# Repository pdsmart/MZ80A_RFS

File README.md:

## Overview

The Sharp MZ80A came with 48K RAM and 4K ROM and apart from the option to add a 2K User RAM/ROM and a 4K Floppy Drive ROM, there was no further possibility to expand the machine memory
capabilities at the hardware level and thus no additional firmware could be added for use at power-on. Add-ons had to rely on loading control firmware into RAM via tape or floppy, thus depleting valuable application space. Some machines of the same era
utilised a scheme called 'banking' whereby much larger memories would occupy a smaller block within the CPU address space and be selected according to features required and hardware attached. The 
BBC Micro was such a machine with upto 16 banks of 16Kb, it made the machine much more useable.

One of the seperate projects I've been working on was a 40/80 Column switchable display and colour output. This upgrade requires different software, either a complete rewrite of the original
monitor or a patched copy for 80 column mode. Wanting to keep the machine as original as possible, using a rewritten ROM is out of the question thus I would need 2 ROMS, original for 40Column
and a patched one for 80Column.

Thus was born the need for Rom Paging in the Sharp MZ80A, ie. Use a modern Flash RAM to house multiple 4K Roms which can be *switched in* to the 4K Monitor ROM address space according to the
hardware upgrade being used.

It was also seen when using large Flash RAM's it was possible to store programs that would normally be present on tape or floppy and load at much higher speed making use of the computer that
much easier.

This upgrade goes a bit further and uses the 4K Monitor ROM and 2K User ROM space to map in 2x512Kbyte Flash RAM's providing multiple paged roms (theoretical 256 x 2K slots and 128 x 4K slots)
and the required custom software to control the banking called the Rom Filing System.

This page along with the [CP/M](/sharpmz-upgrades-cpm) page forms the start of the RFS documentation which is still in its infancy. Within this repository are the schematics, PCB Gerber files and the software to implement the Rom Filing
System hardware and software.

## Rom Filing System

The Rom Filing System is a hardware and software upgrade for the Sharp MZ80A. The hardware replaces the Monitor and User ROM's on the motherboard by a daughter card with lifter sockets where 2x512Kbyte Flash RAM's are sited.
One of the Flash RAM's is paged into the Monitor ROM socket and the other into the User ROM socket. The first 32Kbytes (8 slots x 4K) of the Monitor Flash RAM and the first 24Kybtes (12 slots of 2K) of the User Flash RAM is
dedicated to paged ROMs with the remainder being used to store Sharp MZF format binary images compacted within 256byte sectors. (*NB. This may change to 128 byte sectors as the original reason for choosing 256 byte
sectors no longer exists*).

### RFS Hardware

It is quite easy to make upgrades for older tech these days by using one of the plethora of ready made development boards such as the Raspberry Pi or standalone microcontrollers such as the STM32 series. I did consider using an STM32F series
microcontroller as a ROM emulator as they have the price, performance and packaging advantages but then the goal of this project and the goals of the other Sharp MZ80A upgrades (excluding the Tranzputer) was to use old tech and keep the machine
original. Unlike a commercial project where part choice to provide the required functionality is imperative to keep costs low, with this project the focus is on the learning journey using parts such as the 74 series which were available at the
time of the Sharp, excepting of course the larger Flash RAM and Static RAMs which came a few years later but necessary for the functionality.

Version 2 of the hardware builds on the experiences learnt making version 1. It adds a coded latch (a programmable number of reads required in the 0xEFF8-0xEFFF region) in order to enable access to the control registers and I/O otherwise
both read and write access is performed on memory. It also adds two additional (optional) memories for increased storage and RAM. The additional two devices can be both Flash RAM or 1 Flash RAM and 1 Static RAM. The Static RAM is to
increase the capability of CP/M, such as number of SD drives available and the memory available to TPA applications.

The schematic has been split into two distinct functions, Memory and Control logic. Above is the new Memory schematic which retains the single 512K Flash RAM which replaces the Monitor ROM, write access is not possible as the underlying
Sharp hardware blocks write on Monitor ROM select. In the User ROM socket are 3 devices, the 512K Flash RAM from version 1 but with write access and an additional 2 devices.

The second schematic is the control logic. This creates the needed memory select lines from the main board in combination with address decoding and programmable latches for the upper address lines.

A coded latch is added (74HCT191) which only enables I/O when a read is made to the region 0xEFF8-0xEFFF for a programmable number of times, set by the latch U14 bits 3:5. At start up these bits will be 0 and to enable the I/O a read 
will be needed in the region 0xE800-exEFF7 to reset the 74HCT191 which must then be followed by 16 reads to the range 0xEFF8-0xEFFF. Once the I/O is enabled, the latch value can be changed along with other registers. As soon as a read is made
into the region 0xE800-0xEFF7 then the I/O control is disabled and reads/writes are sent to the selected memory device.

In addition it adds 2 SPI circuits, only one of which will be assembled on the PCB according to choice. The first is a software bitbang SPI using the Z80 to form the correct serial and clock signals in order to talk to an SD Card.
This method uses few hardware components but is much slower. The second is a hardware SPI running at 8MHz which is capable of transferring/receiving a byte in less time that the Z80 takes to perform a read, this allows for performance
similar to the Flash RAM storage. On the hardware SPI it is possible via U14 bit 0 to manually clock the SPI logic, this is intentional as initial connections with an SD Card should begin at 100KHz or less, once established and parameters
set then the 8MHz hardware clock is used.

### RFS Software

In order to use the RFS Hardware, a comprehensive set of Z80 assembler methods needed to be written to allow bank paging and with it came the option, which was taken, to upgrade the machines monitor functionality. This Z80
software forms the Rom Filing System which can be found in the repository within the \<software\> directory.

The following table describes each major file which forms the Rom Filing System:

| Module                 | Target ROM | Size | Bank | Description                                                                                                                                                             |
|------------------------|------------|------|------|-------------------------------------------------------------------------------------------------------------------------------------------------------------------------|
| rfs.asm                | User       | 2K   | 0    | Primary Rom Filing System and MZ700/MZ800 Monitor tools.                                                                                                                |
| rfs_bank1.asm          | User       | 2K   | 1    | Floppy disk controller functions.                                                                                                                                       |
| rfs_bank2.asm          | User       | 2K   | 2    | SD Card controller functions.                                                                                                                                           |
| rfs_bank3.asm          | User       | 2K   | 3    | Memory monitor utility functions and tape/SD copy utilities.                                                                                                            |
| rfs_bank4.asm          | User       | 2K   | 4    | CMT functions.                                                                                                                                                          |
| rfs_bank5.asm          | User       | 2K   | 5    | Unused.                                                                                                                                                                 |
| rfs_bank6.asm          | User       | 2K   | 6    | Message printing routines, static messages, ascii conversion and help screen.                                                                                           |
| rfs_bank7.asm          | User       | 2K   | 7    | Memory Test utility and 8253 Timer test.                                                                                                                                |
| cbios_bank1.asm        | User       | 2K   | 8    | CPM CBIOS Utilities and Audio functions.                                                                                                                                |
| cbios_bank2.asm        | User       | 2K   | 9    | CPM CBIOS Screen and ANSI Terminal functions.                                                                                                                           |
| cbios_bank3.asm        | User       | 2K   | 10   | CPM CBIOS SD Card Controller functions.                                                                                                                                 |
| cbios_bank4.asm        | User       | 2K   | 11   | CPM CBIOS Floppy Disk Controller functions.                                                                                                                             |
| monitor_SA1510.asm     | Monitor    | 4K   | 0    | Original SA1510 Monitor for 40 character display.                                                                                                                       |
| monitor_80c_SA1510.asm | Monitor    | 4K   | 1    | Original SA1510 Monitor patched for 80 character display.                                                                                                               |
| cbios.asm              | Monitor    | 4K   | 2    | CPM CBIOS (exec location 0xC000:0xCFFFF).                                                                                                                               |
| rfs_mrom.asm           | Monitor    | 4K   | 3    | Rom Filing System helper functions located in the Monitor ROM space in Bank 3. These functions are used to scan and process MZF files stored within the User ROM space. |
| unassigned             | Monitor    | 4K   | 4    | Unused slot.                                                                                                                                                            |
| unassigned             | Monitor    | 4K   | 5    | Unused slot.                                                                                                                                                            |
| unassigned             | Monitor    | 4K   | 6    | Unused slot.                                                                                                                                                            |
| unassigned             | Monitor    | 4K   | 7    | Unused slot.                                                                                                                                                            |

In the User ROM, the rfs.asm module and  all the rfs_bank\<x\>.asm modules form the Rom Filing System and are invoked by the original SA-1510 monitor on startup of the MZ80A (or reset). The functionality in these files provides
the Rom Filing System and additional MZ700/800 style monitor utilities. The way the code is structured, a call can be made from one bank to another without issue (stack and execution point manipulation is taken care of) thus
providing almost 16K program space in the User ROM slot.

Sharing the User ROM banks are the cbios_bank\<x\>.asm modules which form part of the CP/M Custom BIOS. They extend the functionality of the CBIOS without impacting RAM usage which is crucial within CP/M in order
to run as many applications as possible.
  
In the Monitor ROM, the rfs_mrom.asm module is located within the 4th bank (bank 3, bank 0 = original SA1510 ROM, bank 1 = 80 column modified SA1510 ROM) and provides utilities needed by the Rom Filing
System. These utilities are specifically needed for scanning and loading MZF files stored in the User ROM Flash RAM (because code executing in the User ROM cant page itself out to scan the
remainder of the ROM).

CPM v2.2 has been added with the CBIOS (Custom BIOS) being implemented within an MROM Bank (bank 2) along with User ROM Banks 8-11 mentioned above. This saves valuable RAM leaving only the CPM CCP and BDOS in RAM which can
be overwritten by programs, this gives a feasible 47K of useable program RAM. An intention is to include a paged RAM chip in the next release of the RFS Hardware which will allow upto 52K of program RAM.

There are several rapidly written shell scripts to aid in the building of the RFS software (which in all honesty need to be written into a single Python or Java tool). These can be seen in the following table along with their purpose:

| Script            |  Description                                                                                                             |
|------------------ | ------------------------------------------------------------------------------------------------------------------------ |
| assemble_cpm.sh   | A shell script to build the CPM binary, the CPM MZF format application for loading via RFS and the CPM ROM Drives 0 & 1  |
| assemble_rfs.sh   | A bash script to build the Rom Filing System ROM images.                                                                 |
| assemble_roms.sh  | A bash script to build all the standard MZ80A ROMS, such as the SA-1510 monitor ROM.                                     |
| make_roms.sh      | A bash script to build the RFS ROMS suitable for programming in the 512KByte Flash RAMS. These images contain the banked RFS ROMS, the various system ROMS such as SA-1510 and all the MZF programs to be loaded by the RFS. |
| make_cpmdisks.sh  | A bash script to build a set of CPM disks, for use as Raw images in the SD Card or Rom drives and as CPC Extended Disk Formats for use in a Floppy disk emulator or copying to physical medium. |
| make_sdcard.sh    | A bash script to create an SD card image combining the RFS Image and several CPM disk drives. This image is then binary copied onto the SD card and installed into the RFS SD Card reader. |
| mzftool.pl        | A perl script to create/extract and manipulate MZF images.                                                               |
| processMZFfiles.sh| A bash script to convert a set of MZF programs into sectored images suitable for use in the Rom Filing System ROMS.      |
| sdtool            | A binary created from the src/tools repository which builds the RFS SD Card image, creating a directory and adding MZF/Binary applications into the drive image. |

To build the software, the assemble_\<name\> shell scripts are used. These scripts requires the [GLASS Z80 Assembler](https://bitbucket.org/grauw/glass/src/default/) which is freely downloadable.

The procedure to build a ROM is:-<br/>
1. Take a set of MZF files and convert them into correct sector padded binary files. The proc_mzf.sh file takes a directory and processes all files within it, transforming originalfile.mzf to originalfile.mzf.\<sector size>.bin<br/>
2. Build the Z80 code using \<tools\>/assemble_rfs.sh for the RFS components, \<tools\>/assemble_roms.sh for assembling all original ROM source including the SA1510 monitor ROM, \<tools\>/assemble_cpm.sh for
   assembling the CPM binaries and dependencies.<br/>
3. Build the ROM using the \<tools\>/make_roms.sh script - before using this you need to create your own selection of MZF files by listing the files with ls -l then converting them into a set of ROM_INCLUDE variables for programs that
   will go into the User and Monitor Flash RAM's.<br/>

### RFS Monitor
  
Upon boot, the typical SA-1510 monitor signon banner will appear and be appended with "+ RFS" if all works well. The usual '\* ' prompt appears and you can then issue any of the original SA-1510 commands along with a set of enhanced
commands, some of which were seen on the MZ700/ MZ800 range and others are custom. The full set of commands are listed in the table below:

| Command | Parameters                          | Description                                                                        |
|---------|-------------------------------------|------------------------------------------------------------------------------------|
| 4       | n/a                                 | Switch to 40 Character mode if the 40/80 Column display upgrade has been added\.   |
| 8       | n/a                                 | Switch to 80 Character mode if the 40/80 Column display upgrade has been added\.   |
| B       | n/a                                 | Enable/Disable key entry beep\.                                                    |
| C       | \[\<8 bit value\>\]                 | Initialise memory from 0x1200 \- Top of RAM with 0x00 or provided value\.          |
| D       | \<address>\[\<address2>\]           | Dump memory from \<address> to \<address2> (or 20 lines) in hex and ascii. When a screen is full, the output is paused until a key is pressed\. <br><br>Subsequent 'D' commands without an address value continue on from last displayed address\.<br><br> Recognised keys during paging are:<br> 'D' - page down, 'U' - page up, 'X' - exit, all other keys list another screen of data\.|
| EC      | \<name> or <br>\<file number>       | Erase file from SD Card\. The SD Card is searched for a file with \<name> or \<file number> and if found, erased\. |
| F       | \[\<drive number\>\]                | Boot from the given Floppy Disk, if no disk number is given, you will be prompted to enter one\. |
| f       | n/a                                 | Execute the original Floppy Disk AFI code @ 0xF000                                 |
| H       | n/a                                 | Help screen of all these commands\.                                                |
| IR      | n/a                                 | Paged directory listing of the files stored in ROM\. Each file title is preceded with a hex number which can be used to identify the file\. |
| IC      | n/a/                                | Paged directory listing of the files stored on the SD Card\. Each file title is preceded with a hex number which can be used to identify the file\. |
| J       | \<address>                          | Jump \(start execution\) at location \<address>\.                                  |
| L \| LT | n/a                                 | Load file into memory from Tape and execute\.                                      |
| LTNX    | n/a                                 | Load file into memory from Tape, dont execute\.                                    |
| LR      | \<name> or <br>\<file number>       | Load file into memory from ROM\. The ROM is searched for a file with \<name> or \<file number> and if found, loaded and executed\. |
| LRNX    | \<name> or <br>\<file number>       | Load file into memory from ROM\. The ROM is searched for a file with \<name> or \<file number> and if found, loaded and not executed\. |
| LC      | \<name> or <br>\<file number>       | Load file into memory from SD Card\. The SD Card is searched for a file with \<name> or \<file number> and if found, loaded and executed\. |
| LCNX    | \<name> or <br>\<file number>       | Load file into memory from SD Card\. The SD Card is searched for a file with \<name> or \<file number> and if found, loaded and not executed\. |
| M       | \<address>                          | Edit and change memory locations starting at \<address>\.                          |
| P       | n/a                                 | Run a test on connected printer\.                                                  |
| R       | n/a                                 | Run a memory test on main mmemory\.                                                |
| S       | \<start addr> \<end addr> \<exec addr> | Save a block of memory to tape\. You will be prompted to enter the filename\. <br><br>Ie\. S120020001203 - Save starting at 0x1200 up until 0x2000 and set execution address to 0x1203\.  |
| SC      | \<start addr> \<end addr> \<exec addr> | Save a block of memory to SD Card\. You will be prompted to enter the filename\. |
| SD2T    | \<name> or <br>\<file number>       | Copy a file from SD Card to Tape\. The SD Card is searched for a file with \<name> or \<file number> and if found, copied to a tape in the CMT\. |
| T       | n/a                                 | Test the 8253 timer\.                                                              |
| T2SD    | n/a                                 | Copy a file from Tape onto the SD Card. A program is loaded from Tape and written to a free position in the SD Card\. |
| V       | n/a                                 | Verify a file just written to tape with the original data stored in memory         |

If the 40/80 column card is installed, typing '4' switches to 40 Column display, typing '8' switches to 80 Column display. For the directory listing commands, 4 columns of output will be shown when in 80 column mode.

## Building RFS

Building the Rom Filing System involves assembling the Z80 Assembly language source into a machine code binary and packaging it into an image suitable for writing onto a 512Kbyte Flash RAM. You may also want to include MZF applications
in the ROMS for rapid exection via the RFS system. If you intend to use CPM, see also the CPM documentation.

To accomplish it you need several tools and at the moment it is quite a manual process.

## Paths

For ease of reading, the following shortnames refer to the corresponding path in this chapter.

|  Short Name      |                                                                            |
|------------------|----------------------------------------------------------------------------|
| \[\<ABS PATH>\]  | The path where this repository was extracted on your system.               |
| \<software\>     | \[\<ABS PATH>\]/MZ80A_RFS/software                                         |
| \<roms\>         | \[\<ABS PATH>\]/MZ80A_RFS/software/roms                                    |
| \<CPM\>          | \[\<ABS PATH>\]/MZ80A_RFS/software/CPM                                     |
| \<tools\>        | \[\<ABS PATH>\]/MZ80A_RFS/software/tools                                   |
| \<src\>         | \[\<ABS PATH>\]/MZ80A_RFS/software/src                                      |
| \<MZF\>          | \[\<ABS PATH>\]/MZ80A_RFS/software/MZF                                     |
| \<MZB\>          | \[\<ABS PATH>\]/MZ80A_RFS/software/MZB                                     |

## Tools

All development has been made under Linux, specifically Debian/Ubuntu. I use Windows for flashing the RAM's and using the GUI version of CP/M Tools but havent dedicated any time into building the RFS under Windows. I will in due course
create a Docker image with all necessary tools installed, but in the meantime, in order to assemble the Z80 code, the C programs and work with the CP/M software andCP/M disk images, you will need to obtain and install the following tools.

[Z80 Glass Assembler](http://www.grauw.nl/blog/entry/740/) - A Z80 Assembler for converting Assembly files into machine code.<br>
[samdisk](https://simonowen.com/samdisk/)   - A multi-os command line based low level disk manipulation tool.<br>
[cpmtools](https://www.cpm8680.com/cpmtools/) - A multi-os command line CP/M disk manipulation tool.<br>
[CPMToolsGUI](http://star.gmobb.jp/koji/cgi/wiki.cgi?page=CpmtoolsGUI) - A Windows based GUI CP/M disk manipulation tool.<br>
[z88dk](https://www.z88dk.org/forum/) - An excellent C development kit for the Z80 CPU.<br>
[sdcc](http://sdcc.sourceforge.net/) - Another excellent Small Device C compiler, the Z80 being one of its targets. z88dk provides an enhanced (for the Z80) version of this tool within its package.<br>

## Software

Building the software and final ROM images can be done by cloning the [repository](https://github.com/pdsmart/MZ80A_RFS.git) and running some of the shell scripts and binaries provided.

The RFS is built as follows:

   1. Make the RFS binary using \<tools\>/assemble_rfs.sh, this creates \<roms\>/rfs.rom for the User Bank Flash RAM and \<roms\>/rfs_mrom.rom for the Monitor Bank Flash RAM.
   2. Make the original MZ80A monitor roms using \<tools\>/assemble_roms.sh, this creates \<roms\>/monitor_SA1510.rom and \<roms\>/monitor_80c_SA1510.rom for the Monitor Bank Flash RAM.
   3. Make the rom images using \<tools\>/make_roms.sh, this creates \<roms\>/USER_ROM_256.bin for the User Bank Flash RAM and \<roms\>/MROM_256.bin for the Monitor Bank Flash RAM.
      The rom images also contain a packed set of MZF applications found in the \<MZF\> directory. Edit the script \<tools\>/make_roms.sh to add or remove applications from the rom images.

The above procedure has been encoded in a set of shell scripts and C tools, which at the simplest level, is to run these commands:
````bash
cd <software>
tools/assemble_cpm.sh
tools/assemble_rfs.sh
tools/assemble_roms.sh
tools/make_cpmdisks.sh
tools/make_roms.sh
tools/make_sdcard.sh
````

The output of the above commands are ROM images \<roms\>/MROM_256.bin and \<roms\>/USER_ROM.256.bin which must be flashed into 512Kbyte Flash RAMS and inserted into the sockets on the
RFS adapter.

The applications which can be stored in the Flash RAMS are located in the \<MZF\> directory. In order to use them within the Flash RAM's, the applications need to be converted into sector rounded binary images and stored in the
\<MZB\> directory. The tool \<tool\>/processMZFiles.sh has been created for this purpose. Simply copy any MZF application into the \<MZF\> directory and run this tool:

````bash
cd <software>
tools/processMZFfiles.sh
````
The files will be converted and stored in the \<MZB\> directory and then used by the \<tools\>/make_roms.sh script when creating the ROM images.  The \<tools\>/make_roms.sh script lists all the applications to be added into the 
Flash RAM's and it will pack as many as space permits. To ensure your application appears in the Flash RAM, add it to the top of the list (just the filename not the .MZF extension), ie:

````bash
Edit the file <tools>/make_roms.sh
Locate the line: ROM_INCLUDE=
Below this line, add your application in the format: ROM_INCLUDE+="${MZBPATH}/<YOUR APPLICATION>.${SECTORSIZE}.bin"
ie. ROM_INCLUDE+="${MZB_PATH}/A-BASIC_SA-5510.${SECTORSIZE}.bin:"
Save the file and run the commands above to build the MonitorROM and USERROM's.
````

The SD Card image is created by the \<tools\>/make_sdcard.sh script and in its basic form creates an image which can be directly copied onto an SD Card. This image contains the SD Card Filing System which is populated with
MZF applications from the \<MZF\> directory. Edit the \<tools\>/make_sdcard.sh script to add/remove MZF applications which are installed into the SDCFS. CP/M images are also added to the SD Card and this is covered in the 
[CP/M](sharpmz-upgrades-cpm/) section.

## SD Card 

A recent addition to the Rom Filing System is an SD Card. In hardware it is implemented using the bitbang technique and provides performance comparable with a floppy disk without the seek overhead or interleave
times, but in all honesty, this would be better catered for by dedicated shift registers in order to gain performance on par with the ROM drives.

I worked on using the [Petit FatFS by El CHaN](http://elm-chan.org/fsw/ff/00index_p.html)  for the SD Card filing system, which is excellent having previously used the full Fat version with my ZPU project, but the Z80 isnt the best
architecture for code size when using C. In the repository in \<src\>/tools is my developments along this line with a C program called 'sdtest' and a modularized PetitFS along with manually coded Z80 assembler to handle the bitbang
algorithm and SD Card initialisation and communications.  The program compiles into an MZF application and when run performs flawlessly. The only issue as mentioned is size and when your limited to 2K and 4K banked roms with a 12K
filing system you have an immediate storage issue. It is feasible to build PetitFS into a set of ROM banks using the z88dk C Compiler which supports banked targets and __far constructs but it would be a lot of effort for something
which really isnt required.

I thus took a step back and decided to create my own simple filing system which is described below. This filing system is used for Sharp MZ80A MZF applications and is for both read and write operations.

### SD Card Filing System

The SD Card Filing System resides at the beginning of the SD Card and is followed by several CPM disk drive images. The SDCFS image is constructed of a directory plus 256 file blocks. The directory can contain upto 256 entries, 
each entry being 32 bytes long. The SDCFS directory entry is based on the MZF Header format and is as follows:

| FLAG1  | FLAG2  | FILE NAME | START SECTOR | SIZE    | LOAD ADDR | EXEC ADDR | RESERVED |
|--------|--------|-----------|--------------|---------|-----------|-----------|----------|
| 1 Byte | 1 Byte | 17 Bytes  | 4 Bytes      | 2 Bytes | 2 Bytes   | 2 Bytes   | 3 Bytes  |

| Parameter     | Description                                                                                   |
| ------------- | --------------------------------------------------------------------------------------------- |
|  FLAG1        | BIT 7 = 1, Valid directory entry, 0 = inactive.                                               |
|  FLAG2        | MZF Execution Code, 0x01 = Binary                                                             |
|  FILENAME     | Standard MZF format filename.                                                                 |
|  START SECTOR | Sector in the SD card where the program starts. It always starts at position 0 of the sector. |
|  SIZE         | Size in bytes of the program. Each file block occupies 64Kbyte space (as per a tape) and this parameter provides the actual space occupied by the program at the current time. |
|  LOAD ADDR    | Start address in memory where data should be loaded.                                          |
|  EXEC ADDR    | If a binary then this parameter specifies the location to auto execute once loaded.           |
|  RESERVED     | Not used at the moment.                                                                       |

Each file block, 1 per directory entry, is 64K long which is intentional as it keeps a fixed size which is in line
with the maximum tape (CMT) length and can be freely read/written to just as if it were a tape. This allows for easy
use within tape based applications such as Basic SA-1510 or for copying SD Card \<-\> CMT.

The remainder of the SD Card is filled with 16MByte CPM Disk drive images. Each image is organised as 32 (512byte) Sectors x 1024 tracks
and 1 head. Each image will be mounted in CPM under its own drive letter.

Visually, the SD Card is organised as follows:

```
SECTOR   FUNCTION
00000000 ---------------------------------------------------------------------------
         | ROM FILING SYSTEM IMAGE                                                 |
         |                                                                         |
00000000 | RFS DIRECTORY ENTRY 000 (32BYTE)                                        |
         | ..                                                                      |
         | ..                                                                      |
00001FE0 | RFS DIRECTORY ENTRY 255 (32BYTE)                                        |
00002000 ---------------------------------------------------------------------------
         | RFS FILE BLOCK 0                                                        |
00003000 ---------------------------------------------------------------------------
         ...

00FF0000 ---------------------------------------------------------------------------
         | RFS FILE BLOCK 255                                                      |
01000000 ---------------------------------------------------------------------------
01000000 ---------------------------------------------------------------------------
         |                                                                         |
         |  CP/M DISK IMAGE 0                                                      |
         |                                                                         |
02000000 ---------------------------------------------------------------------------
         |                                                                         |
         |  CP/M DISK IMAGE 1                                                      |
         |                                                                         |
03000000 ---------------------------------------------------------------------------
         |                                                                         |
         |  CP/M DISK IMAGE 2                                                      |
         |                                                                         |
XX000000 ---------------------------------------------------------------------------
         |                                                                         |
         |  CP/M DISK IMAGE <n>                                                    |
         |                                                                         |
         ---------------------------------------------------------------------------
```

#### To Do
1) Update Basic SA-5510 so that it loads/saves from SD Card.<br/>

## Credits

Where I have used or based any component on a 3rd parties design I have included the original authors copyright notice within the headers or given due credit. All 3rd party software, to my knowledge and research, is open source and freely useable, if there is found to be any component with licensing restrictions, it will be removed from this repository and a suitable link/config provided.

## Licenses

This design, hardware and software, is licensed under the GNU Public Licence v3.

### The Gnu Public License v3
 The source and binary files in this project marked as GPL v3 are free software: you can redistribute it and-or modify it under the terms of the GNU General Public License as published by the Free Software Foundation, either version 3 of the License, or (at your option) any later version.

 The source files are distributed in the hope that it will be useful, but WITHOUT ANY WARRANTY; without even the implied warranty of MERCHANTABILITY or FITNESS FOR A PARTICULAR PURPOSE.  See the GNU General Public License for more details.

 You should have received a copy of the GNU General Public License along with this program.  If not, see http://www.gnu.org/licenses/.

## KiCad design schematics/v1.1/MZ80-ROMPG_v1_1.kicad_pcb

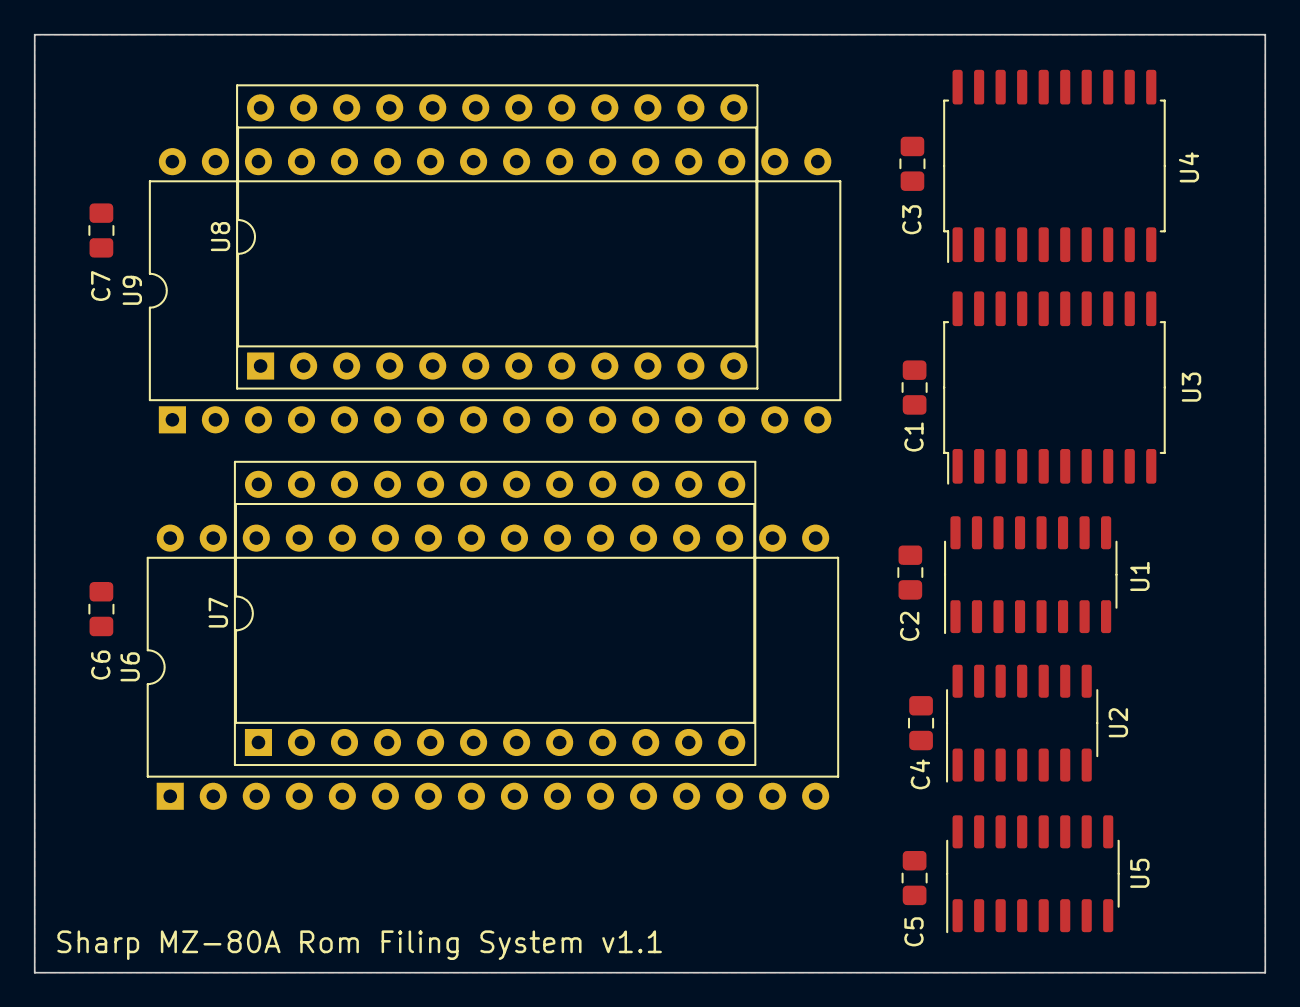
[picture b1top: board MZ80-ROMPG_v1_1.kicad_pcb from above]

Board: 2 copper layers, 72.6 x 55.4 mm, 16 parts (0 on the bottom side), 48 nets, no tracks yet.

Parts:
C1, C2, C3, C4, C5, C6, C7: 100nF; C_0805_2012Metric_Pad1.15x1.40mm_HandSolder
U1: 74HCT133; SOIC-16_3.9x9.9mm_P1.27mm
U2: 74HCT04; SOIC-14_3.9x8.7mm_P1.27mm
U3, U4: 74HCT273; SOIC-20W_7.5x12.8mm_P1.27mm
U5: 74HCT138; SOIC-16_3.9x9.9mm_P1.27mm
U6, U9: SST39SF040; DIP-32_W15.24mm
U7: 2732_Socket; DIP-24_W15.24mm_Socket
U8: 2716_Socket; DIP-24_W15.24mm_Socket

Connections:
+5V: C1.1, C2.1, C3.2, C4.1, C5.1, C6.1, C7.1, U1.15, U1.16, U2.14, U3.20, U4.20, U5.3, U5.6, U5.16, U6.32, U7.24, U8.24, U9.32
/A0: U5.1, U6.12, U7.8, U9.12
/A1: U5.2, U6.11, U7.7, U9.11
/A2: U1.1, U6.10, U7.6, U9.10
/A3: U1.2, U6.9, U7.5, U9.9
/A4: U1.3, U6.8, U7.4, U9.8
/A5: U1.4, U6.7, U7.3, U9.7
/A6: U1.5, U6.6, U7.2, U9.6
/A7: U1.6, U6.5, U7.1, U9.5
/A8: U1.7, U6.27, U7.23, U9.27
/A9: U1.10, U6.26, U7.22, U9.26
/A10: U1.11, U6.23, U7.19, U9.23
/A11: U1.12, U6.25, U7.21
/BK1A12: U3.2, U6.4
/BK1A13: U3.5, U6.28
/BK1A14: U3.6, U6.29
/BK1A15: U3.9, U6.3
/BK1A16: U3.12, U6.2
/BK1A17: U3.15, U6.30
/BK1A18: U3.16, U6.1
/BK2A11: U4.2, U9.25
/BK2A12: U4.5, U9.4
/BK2A13: U4.6, U9.28
/BK2A14: U4.9, U9.29
/BK2A15: U4.12, U9.3
/BK2A16: U4.15, U9.2
/BK2A17: U4.16, U9.30
/BK2A18: U4.19, U9.1
/D0: U3.3, U4.3, U6.13, U7.9, U8.9, U9.13
/D1: U3.4, U4.4, U6.14, U7.10, U8.10, U9.14
/D2: U3.7, U4.7, U6.15, U7.11, U8.11, U9.15
/D3: U3.8, U4.8, U6.17, U7.13, U8.13, U9.17
/D4: U3.13, U4.13, U6.18, U7.14, U8.14, U9.18
/D5: U3.14, U4.14, U6.19, U7.15, U8.15, U9.19
/D6: U3.17, U4.17, U6.20, U7.16, U8.16, U9.20
/D7: U3.18, U4.18, U6.21, U7.17, U8.17, U9.21
/~CSMROM~: U6.22, U7.20
/~CSUSR~: U2.1, U8.18, U9.22
/~MRD~: U6.24, U8.20, U9.24
/~MWR~: U2.3, U6.31, U8.21, U9.31
GNDPWR: C1.2, C2.2, C3.1, C4.2, C5.2, C6.2, C7.2, U1.8, U2.5, U2.7, U2.9, U2.11, U2.13, U3.10, U4.10, U5.8, U6.16, U7.12, U8.12, U9.16
unnamed: U1.9, U5.4, U5.5
unnamed: U1.13, U2.2
unnamed: U1.14, U2.4
unnamed: U3.1, U5.9
unnamed: U3.11, U5.11
unnamed: U4.1, U5.7
unnamed: U4.11, U5.10

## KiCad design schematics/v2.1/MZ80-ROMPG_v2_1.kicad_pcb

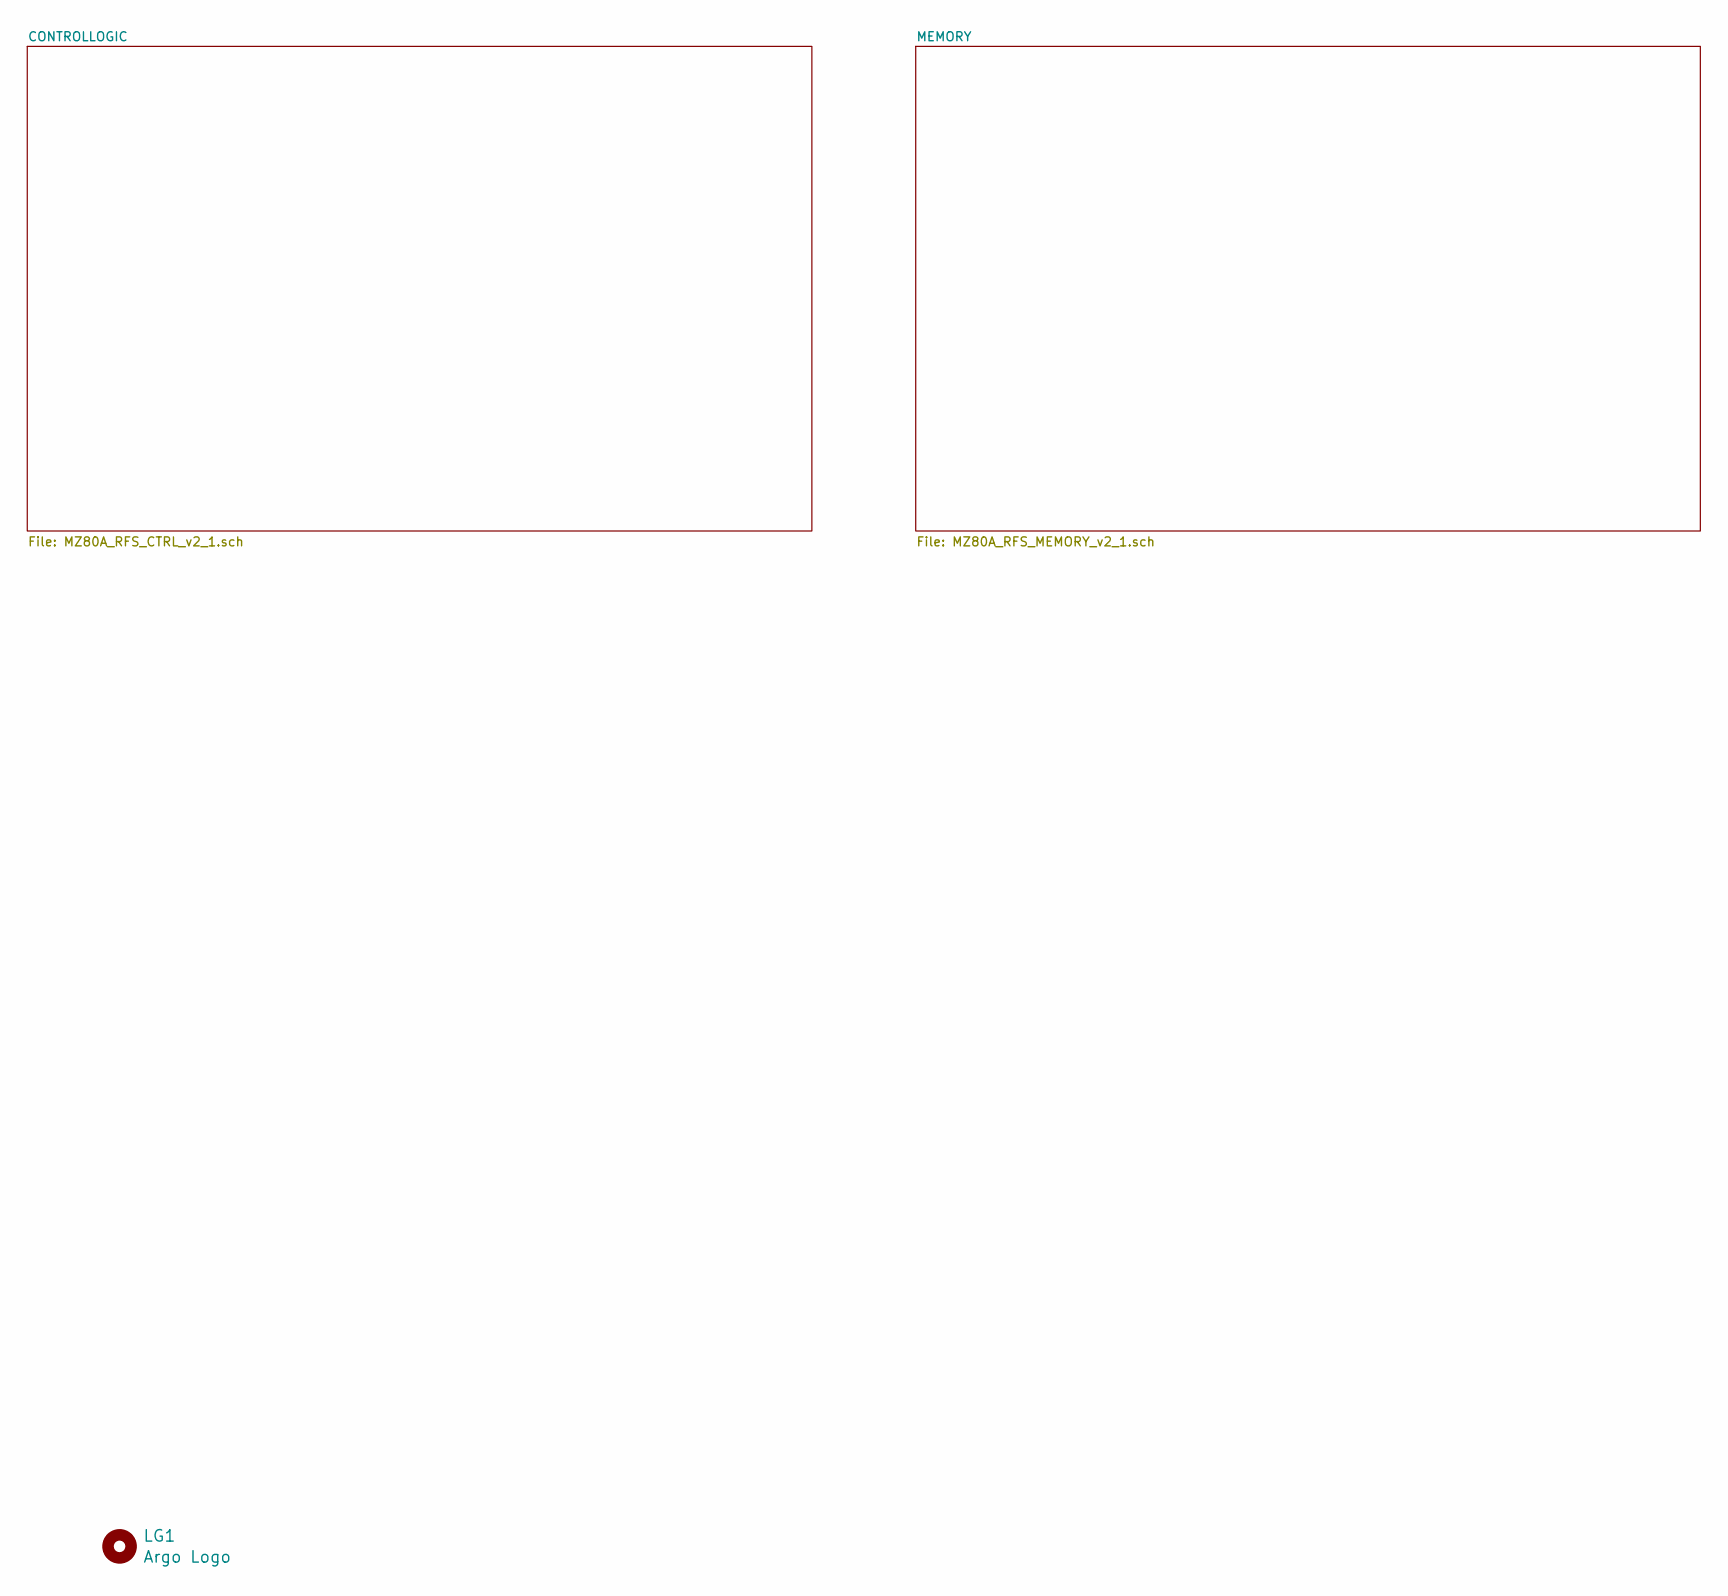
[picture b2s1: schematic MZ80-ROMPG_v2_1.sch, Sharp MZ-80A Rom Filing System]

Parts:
LG1: Argo Logo; Argo

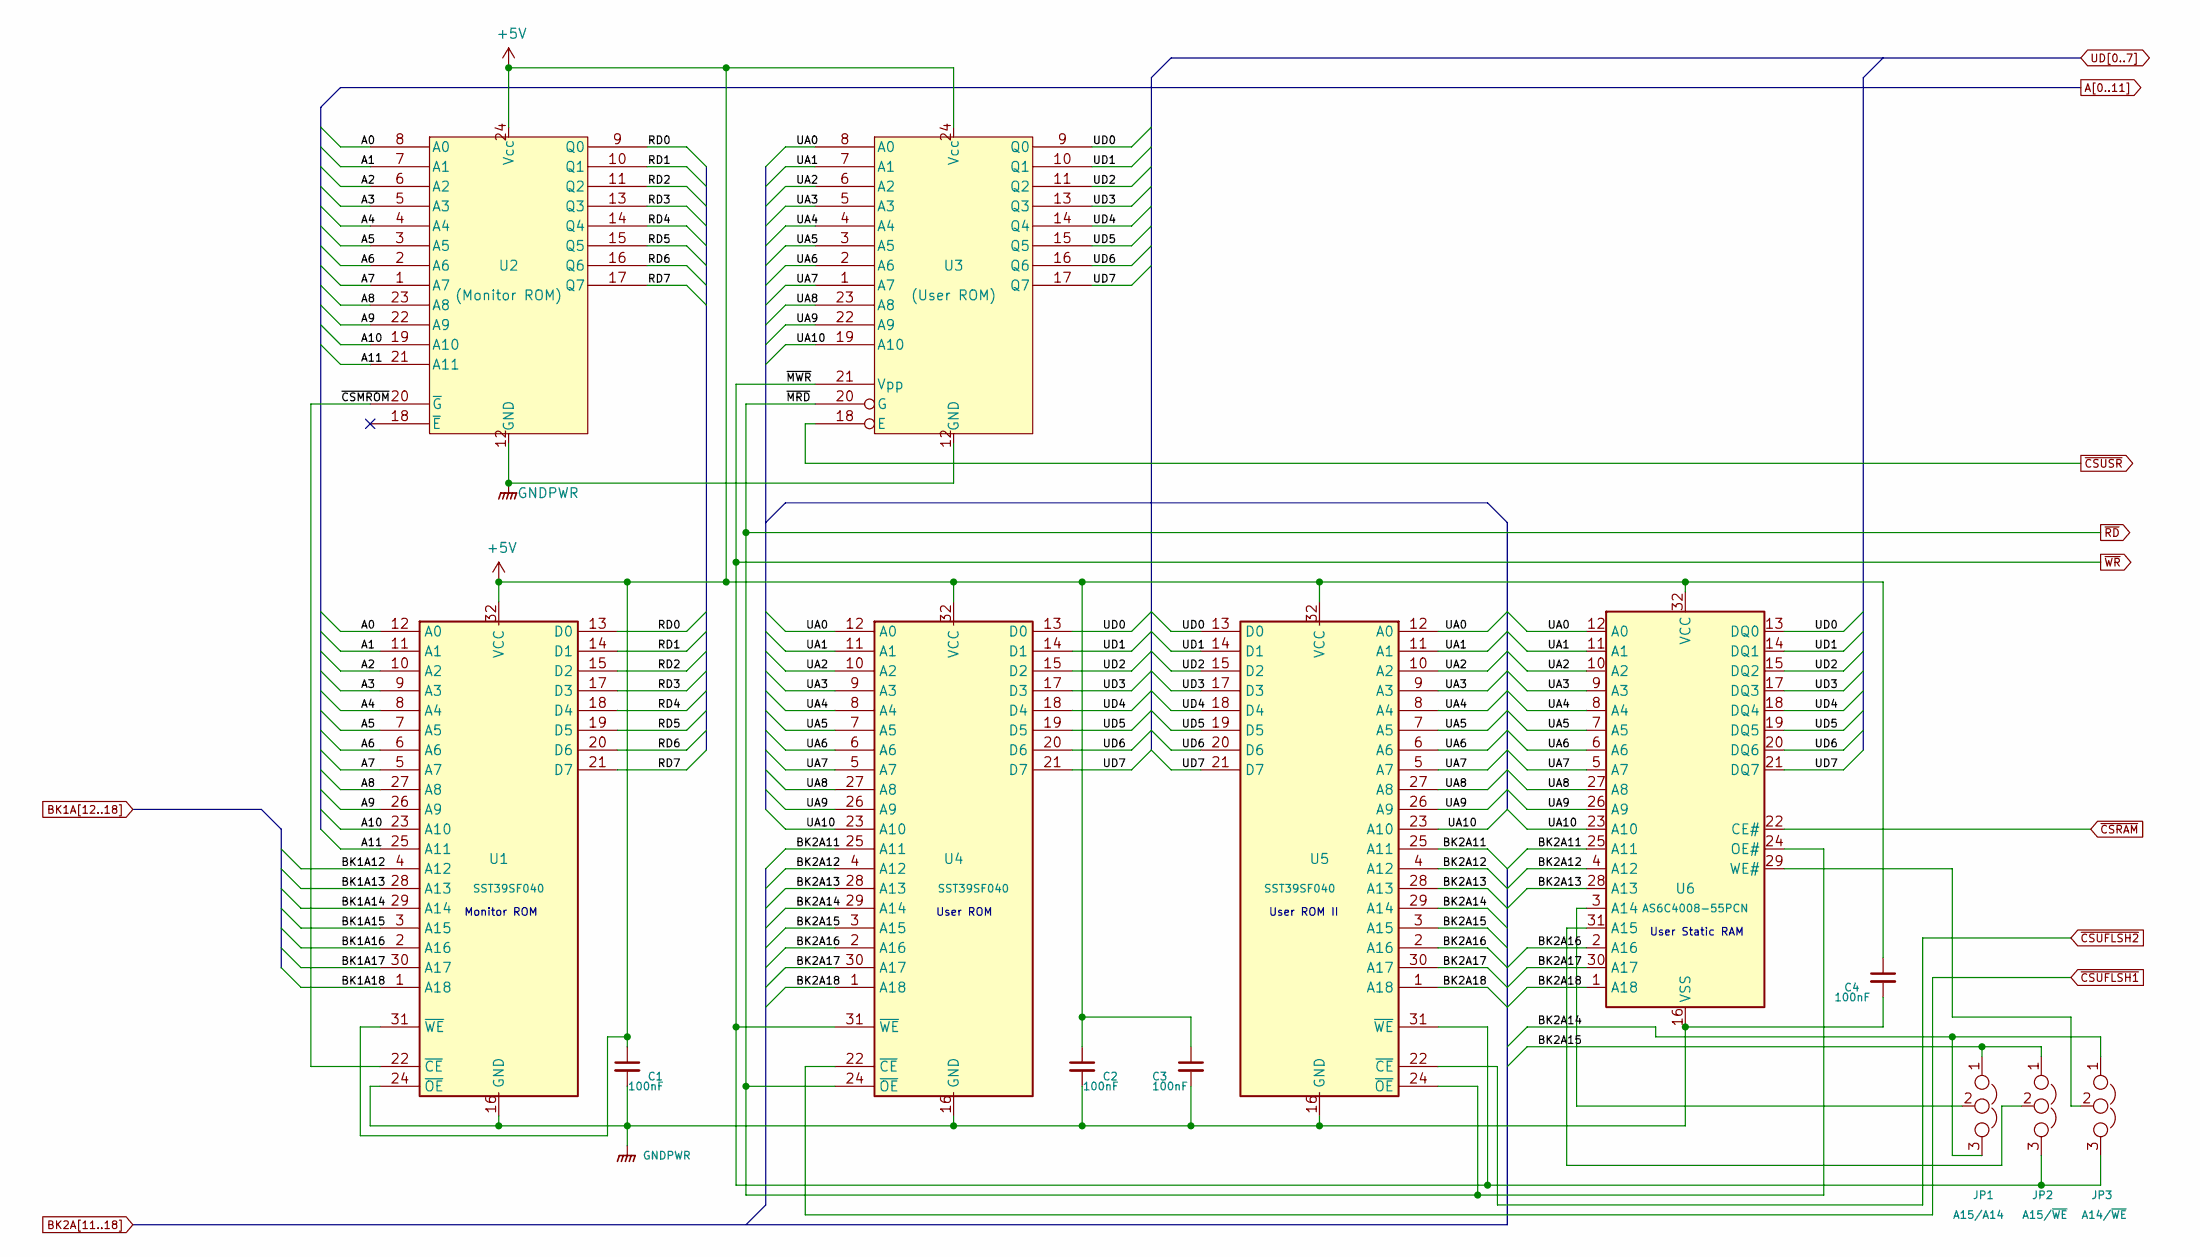
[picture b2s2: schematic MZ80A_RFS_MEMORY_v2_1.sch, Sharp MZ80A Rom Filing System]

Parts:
C1, C2, C3, C4: 100nF; C_0805_2012Metric_Pad1.15x1.40mm_HandSolder
JP1: A15/A14; PinHeader_1x03_P2.00mm_Vertical
JP2: A15/~WE~; PinHeader_1x03_P2.00mm_Vertical
JP3: A14/~WE~; PinHeader_1x03_P2.00mm_Vertical
U1, U4, U5: SST39SF040; DIP-32_W15.24mm_Socket
U2: (Monitor ROM); DIP-24_W15.24mm_Socket
U3: (User ROM); DIP-24_W15.24mm_Socket
U6: AS6C4008-55PCN; DIP-32_W15.24mm_Socket

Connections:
+5V: C1.1, C2.1, C3.1, C4.1, U1.31 (~WE~), U1.32 (VCC), U2.24 (Vcc), U3.24 (Vcc), U4.32 (VCC), U5.32 (VCC), U6.32 (VCC); also elsewhere on the board
/MEMORY/RD0: U1.13 (D0), U2.9 (Q0)
/MEMORY/RD1: U1.14 (D1), U2.10 (Q1)
/MEMORY/RD2: U1.15 (D2), U2.11 (Q2)
/MEMORY/RD3: U1.17 (D3), U2.13 (Q3)
/MEMORY/RD4: U1.18 (D4), U2.14 (Q4)
/MEMORY/RD5: U1.19 (D5), U2.15 (Q5)
/MEMORY/RD6: U1.20 (D6), U2.16 (Q6)
/MEMORY/RD7: U1.21 (D7), U2.17 (Q7)
/MEMORY/UA0: U3.8 (A0), U4.12 (A0), U5.12 (A0), U6.12 (A0)
/MEMORY/UA1: U3.7 (A1), U4.11 (A1), U5.11 (A1), U6.11 (A1)
/MEMORY/UA2: U3.6 (A2), U4.10 (A2), U5.10 (A2), U6.10 (A2)
/MEMORY/UA3: U3.5 (A3), U4.9 (A3), U5.9 (A3), U6.9 (A3)
/MEMORY/UA4: U3.4 (A4), U4.8 (A4), U5.8 (A4), U6.8 (A4)
/MEMORY/UA5: U3.3 (A5), U4.7 (A5), U5.7 (A5), U6.7 (A5)
/MEMORY/UA6: U3.2 (A6), U4.6 (A6), U5.6 (A6), U6.6 (A6)
/MEMORY/UA7: U3.1 (A7), U4.5 (A7), U5.5 (A7), U6.5 (A7)
/MEMORY/UA8: U3.23 (A8), U4.27 (A8), U5.27 (A8), U6.27 (A8)
/MEMORY/UA9: U3.22 (A9), U4.26 (A9), U5.26 (A9), U6.26 (A9)
/MEMORY/UA10: U3.19 (A10), U4.23 (A10), U5.23 (A10), U6.23 (A10)
/MEMORY/~CSMROM~: U1.22 (~CE~), U2.20 (~G)
A0: U1.12 (A0), U2.8 (A0); also elsewhere on the board
A1: U1.11 (A1), U2.7 (A1); also elsewhere on the board
A2: U1.10 (A2), U2.6 (A2); also elsewhere on the board
A3: U1.9 (A3), U2.5 (A3); also elsewhere on the board
A4: U1.8 (A4), U2.4 (A4); also elsewhere on the board
A5: U1.7 (A5), U2.3 (A5); also elsewhere on the board
A6: U1.6 (A6), U2.2 (A6); also elsewhere on the board
A7: U1.5 (A7), U2.1 (A7); also elsewhere on the board
A8: U1.27 (A8), U2.23 (A8); also elsewhere on the board
A9: U1.26 (A9), U2.22 (A9); also elsewhere on the board
A10: U1.23 (A10), U2.19 (A10); also elsewhere on the board
A11: U1.25 (A11), U2.21 (A11)
BK1A12: U1.4 (A12); also elsewhere on the board
BK1A13: U1.28 (A13); also elsewhere on the board
BK1A14: U1.29 (A14); also elsewhere on the board
BK1A15: U1.3 (A15); also elsewhere on the board
BK1A16: U1.2 (A16); also elsewhere on the board
BK1A17: U1.30 (A17); also elsewhere on the board
BK1A18: U1.1 (A18); also elsewhere on the board
BK2A11: U4.25 (A11), U5.25 (A11), U6.25 (A11); also elsewhere on the board
BK2A12: U4.4 (A12), U5.4 (A12), U6.4 (A12); also elsewhere on the board
BK2A13: U4.28 (A13), U5.28 (A13), U6.28 (A13); also elsewhere on the board
BK2A14: JP1.3, JP3.1, U4.29 (A14), U5.29 (A14); also elsewhere on the board
BK2A15: JP1.1, JP2.1, U4.3 (A15), U5.3 (A15); also elsewhere on the board
BK2A16: U4.2 (A16), U5.2 (A16), U6.2 (A16); also elsewhere on the board
BK2A17: U4.30 (A17), U5.30 (A17), U6.30 (A17); also elsewhere on the board
BK2A18: U4.1 (A18), U5.1 (A18), U6.1 (A18); also elsewhere on the board
GNDPWR: C1.2, C2.2, C3.2, C4.2, U1.16 (GND), U1.24 (~OE~), U2.12 (GND), U3.12 (GND), U4.16 (GND), U5.16 (GND), U6.16 (VSS); also elsewhere on the board
unnamed: JP1.2, U6.3 (A14)
unnamed: JP2.2, U6.31 (A15)
unnamed: JP3.2, U6.29 (WE#)
UD0: U3.9 (Q0), U4.13 (D0), U5.13 (D0), U6.13 (DQ0); also elsewhere on the board
UD1: U3.10 (Q1), U4.14 (D1), U5.14 (D1), U6.14 (DQ1); also elsewhere on the board
UD2: U3.11 (Q2), U4.15 (D2), U5.15 (D2), U6.15 (DQ2); also elsewhere on the board
UD3: U3.13 (Q3), U4.17 (D3), U5.17 (D3), U6.17 (DQ3); also elsewhere on the board
UD4: U3.14 (Q4), U4.18 (D4), U5.18 (D4), U6.18 (DQ4); also elsewhere on the board
UD5: U3.15 (Q5), U4.19 (D5), U5.19 (D5), U6.19 (DQ5); also elsewhere on the board
UD6: U3.16 (Q6), U4.20 (D6), U5.20 (D6), U6.20 (DQ6); also elsewhere on the board
UD7: U3.17 (Q7), U4.21 (D7), U5.21 (D7), U6.21 (DQ7); also elsewhere on the board
~CSRAM~: U6.22 (CE#); also elsewhere on the board
~CSUFLSH1~: U4.22 (~CE~); also elsewhere on the board
~CSUFLSH2~: U5.22 (~CE~); also elsewhere on the board
~CSUSR~: U3.18 (E); also elsewhere on the board
~RD~: U3.20 (G), U4.24 (~OE~), U5.24 (~OE~), U6.24 (OE#); also elsewhere on the board
~WR~: JP2.3, JP3.3, U3.21 (Vpp), U4.31 (~WE~), U5.31 (~WE~); also elsewhere on the board

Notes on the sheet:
Monitor ROM
User ROM
User ROM II
User Static RAM

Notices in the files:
README.md:
Licenses:
This design, hardware and software, is licensed under the GNU Public Licence v3.
The Gnu Public License v3:
The source and binary files in this project marked as GPL v3 are free software: you can redistribute it and-or modify it under the terms of the GNU General Public License as published by the Free Software Foundation, either version 3 of the License, or (at your option) any later version.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
